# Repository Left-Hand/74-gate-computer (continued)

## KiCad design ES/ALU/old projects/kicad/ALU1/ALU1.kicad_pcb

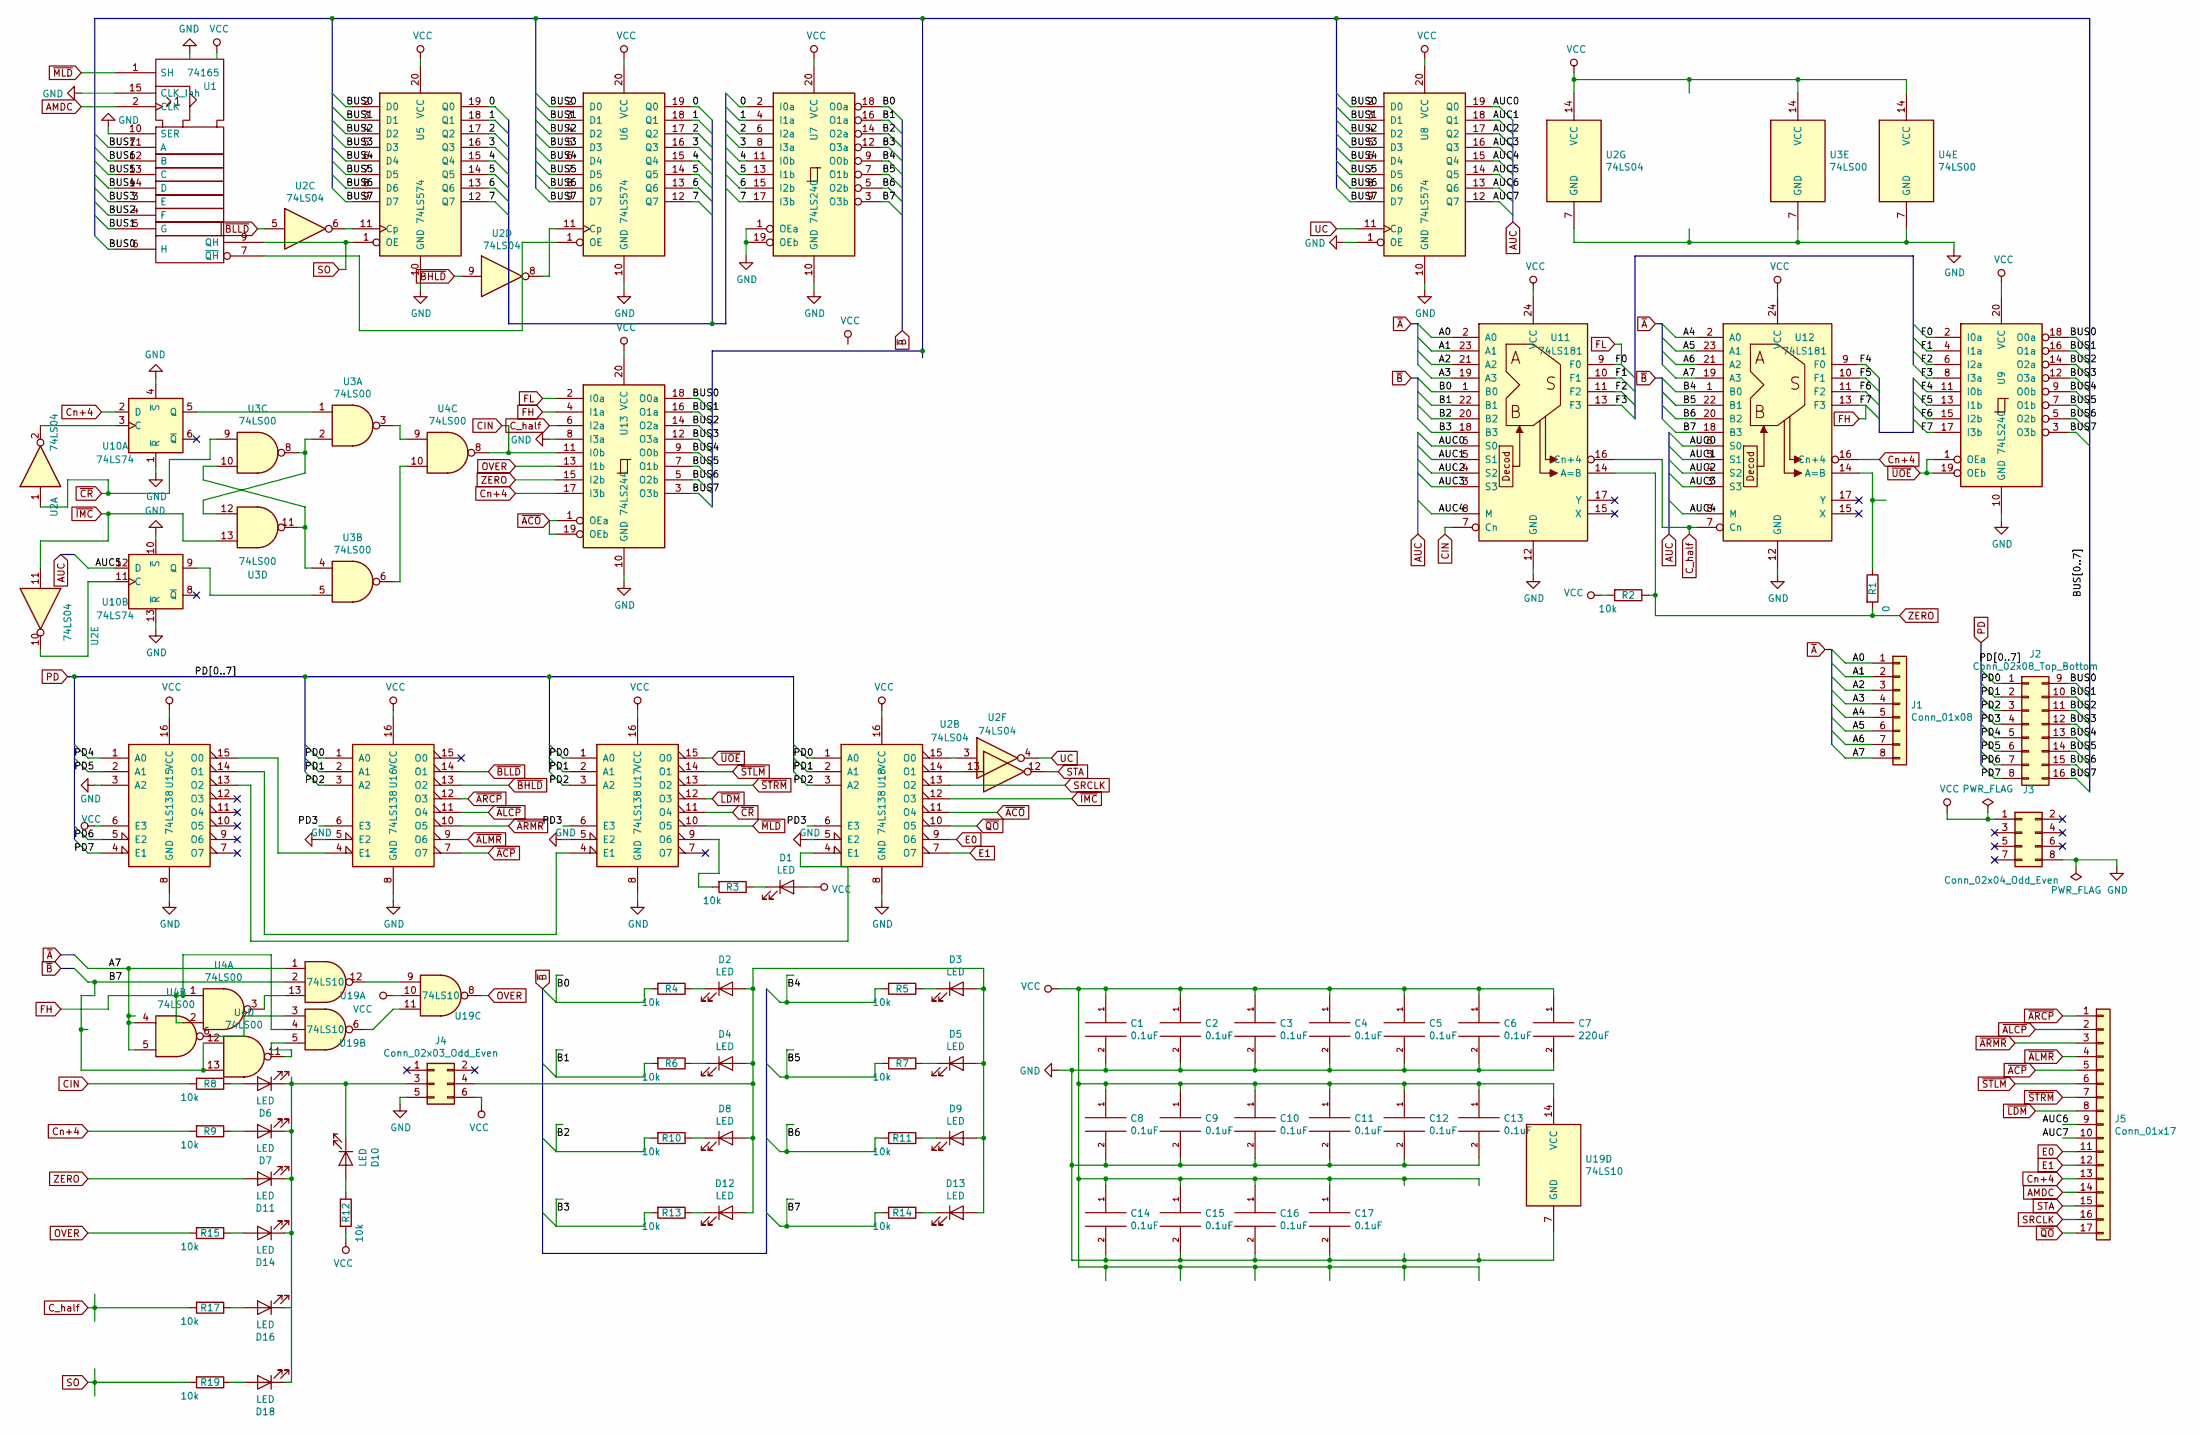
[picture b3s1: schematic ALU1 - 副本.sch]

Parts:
C1, C2, C3, C4, C5, C6, C8, C9, C10, C11, C12, C13, C14, C15, C16, C17: 0.1uF; C_Disc_D5.0mm_W2.5mm_P5.00mm
C7: 220uF; C_Radial_D6.3mm_H7.0mm_P2.50mm
D1, D2, D3, D4, D5, D6, D7, D8, D9, D10, D11, D12, D13, D14, D16, D18: LED; LED_Rectangular_W5.0mm_H2.0mm
J1: Conn_01x08; PinHeader_1x08_P2.54mm_Vertical
J2: Conn_02x08_Top_Bottom; PinHeader_2x08_P2.54mm_Horizontal
J3: Conn_02x04_Odd_Even; PinHeader_2x04_P2.54mm_Horizontal
J4: Conn_02x03_Odd_Even; PinHeader_2x03_P2.54mm_Vertical
J5: Conn_01x17; PinHeader_1x17_P2.54mm_Vertical
R1: 0; R_0805_2012Metric
R2, R3, R4, R5, R6, R7, R8, R9, R10, R11, R12, R13, R14, R15, R17, R19: 10k; R_0805_2012Metric
U1: 74165; DIP-16_W7.62mm
U2: 74LS04; DIP-14_W7.62mm
U3, U4: 74LS00; DIP-14_W7.62mm
U5, U6, U8: 74LS574; DIP-20_W7.62mm
U7, U9: 74LS240; DIP-20_W7.62mm
U10: 74LS74; DIP-14_W7.62mm
U11, U12: 74LS181; DIP-24_W15.24mm
U13: 74LS244; DIP-20_W7.62mm
U15, U16, U17, U18: 74LS138; DIP-16_W7.62mm
U19: 74LS10; DIP-14_W7.62mm

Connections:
/0: U5.19 (Q0), U6.19 (Q0), U7.2 (I0a)
/1: U5.18 (Q1), U6.18 (Q1), U7.4 (I1a)
/2: U5.17 (Q2), U6.17 (Q2), U7.6 (I2a)
/3: U5.16 (Q3), U6.16 (Q3), U7.8 (I3a)
/4: U5.15 (Q4), U6.15 (Q4), U7.11 (I0b)
/5: U5.14 (Q5), U6.14 (Q5), U7.13 (I1b)
/6: U5.13 (Q6), U6.13 (Q6), U7.15 (I2b)
/7: U5.12 (Q7), U6.12 (Q7), U7.17 (I3b)
/A0: J1.1, U11.2 (A0)
/A1: J1.2, U11.23 (A1)
/A2: J1.3, U11.21 (A2)
/A3: J1.4, U11.19 (A3)
/A4: J1.5, U12.2 (A0)
/A5: J1.6, U12.23 (A1)
/A6: J1.7, U12.21 (A2)
/A7: J1.8, U4.4, U4.5, U12.19 (A3), U19.1
/AUC0: U8.19 (Q0), U11.6 (S0), U12.6 (S0)
/AUC1: U8.18 (Q1), U11.5 (S1), U12.5 (S1)
/AUC2: U8.17 (Q2), U11.4 (S2), U12.4 (S2)
/AUC3: U8.16 (Q3), U11.3 (S3), U12.3 (S3)
/AUC4: U8.15 (Q4), U11.8 (M), U12.8 (M)
/AUC5: U8.14 (Q5), U10.12 (D)
/AUC6: J5.9, U8.13 (Q6)
/AUC7: J5.10, U8.12 (Q7)
/B0: R4.2, U7.18 (O0a), U11.1 (B0)
/B1: R6.2, U7.16 (O1a), U11.22 (B1)
/B2: R10.2, U7.14 (O2a), U11.20 (B2)
/B3: R13.2, U7.12 (O3a), U11.18 (B3)
/B4: R5.2, U7.9 (O0b), U12.1 (B0)
/B5: R7.2, U7.7 (O1b), U12.22 (B1)
/B6: R11.2, U7.5 (O2b), U12.20 (B2)
/B7: R14.2, U4.12, U4.13, U7.3 (O3b), U12.18 (B3), U19.2
/BUS0: J2.9, U1.6 (H), U5.2 (D0), U6.2 (D0), U8.2 (D0), U9.18 (O0a), U13.18 (O0a)
/BUS1: J2.10, U1.5 (G), U5.3 (D1), U6.3 (D1), U8.3 (D1), U9.16 (O1a), U13.16 (O1a)
/BUS2: J2.11, U1.4 (F), U5.4 (D2), U6.4 (D2), U8.4 (D2), U9.14 (O2a), U13.14 (O2a)
/BUS3: J2.12, U1.3 (E), U5.5 (D3), U6.5 (D3), U8.5 (D3), U9.12 (O3a), U13.12 (O3a)
/BUS4: J2.13, U1.14 (D), U5.6 (D4), U6.6 (D4), U8.6 (D4), U9.9 (O0b), U13.9 (O0b)
/BUS5: J2.14, U1.13 (C), U5.7 (D5), U6.7 (D5), U8.7 (D5), U9.7 (O1b), U13.7 (O1b)
/BUS6: J2.15, U1.12 (B), U5.8 (D6), U6.8 (D6), U8.8 (D6), U9.5 (O2b), U13.5 (O2b)
/BUS7: J2.16, U1.11 (A), U5.9 (D7), U6.9 (D7), U8.9 (D7), U9.3 (O3b), U13.3 (O3b)
/F1: U9.4 (I1a), U11.10 (F1)
/F2: U9.6 (I2a), U11.11 (F2)
/F3: U9.8 (I3a), U11.13 (F3)
/F4: U9.11 (I0b), U12.9 (F0)
/F5: U9.13 (I1b), U12.10 (F1)
/F6: U9.15 (I2b), U12.11 (F2)
/PD0: J2.1, U16.1 (A0), U17.1 (A0), U18.1 (A0)
/PD1: J2.2, U16.2 (A1), U17.2 (A1), U18.2 (A1)
/PD2: J2.3, U16.3 (A2), U17.3 (A2), U18.3 (A2)
/PD3: J2.4, U16.6 (E3), U17.6 (E3), U18.6 (E3)
/PD4: J2.5, U15.1 (A0)
/PD5: J2.6, U15.2 (A1)
/PD6: J2.7, U15.5 (E2)
/PD7: J2.8, U15.4 (E1)
AMDC: J5.14, U1.2 (CLK)
CIN: R8.2, U4.8, U11.7 (Cn), U13.11 (I0b)
C_half: R17.2, U11.16 (Cn+4), U12.7 (Cn), U13.6 (I2a)
Cn+4: J5.13, R9.2, U10.2 (D), U12.16 (Cn+4), U13.17 (I3b)
E0: J5.11, U18.9 (O6)
E1: J5.12, U18.7 (O7)
FH: U4.1, U4.2, U9.17 (I3b), U12.13 (F3), U13.4 (I1a), U19.4
FL: U9.2 (I0a), U11.9 (F0), U13.2 (I0a)
GND: C1.2, C2.2, C3.2, C4.2, C5.2, C6.2, C7.2, C8.2, C9.2, C10.2, C11.2, C12.2, C13.2, C14.2, C15.2, C16.2, C17.2, J3.8, J4.5, U1.8 (GND), U1.10 (SER), U1.15 (CLK_Inh), U2.7 (GND), U3.7 (GND), U4.7 (GND), U5.10 (GND), U6.10 (GND), U7.1 (OEa), U7.10 (GND), U7.19 (OEb), U8.1 (OE), U8.10 (GND), U9.10 (GND), U10.1 (~R), U10.4 (~S), U10.10 (~S), U10.13 (~R), U11.12 (GND), U12.12 (GND), U13.8 (I3a), U13.10 (GND), U15.3 (A2), U15.8 (GND), U16.5 (E2), U16.8 (GND), U17.5 (E2), U17.8 (GND), U18.5 (E2), U18.8 (GND), U19.7 (GND); also elsewhere on the board
unnamed: D1.1 (K), R3.1
unnamed: D2.1 (K), R4.1
unnamed: D3.1 (K), R5.1
unnamed: D4.1 (K), R6.1
unnamed: D5.1 (K), R7.1
unnamed: D6.2 (A), R8.1
unnamed: D7.2 (A), R9.1
unnamed: D8.1 (K), R10.1
unnamed: D9.1 (K), R11.1
unnamed: D6.1 (K), D7.1 (K), D10.1 (K), D11.1 (K), D14.1 (K), D16.1 (K), D18.1 (K), J4.3
unnamed: D10.2 (A), R12.1
unnamed: D12.1 (K), R13.1
unnamed: D2.2 (A), D3.2 (A), D4.2 (A), D5.2 (A), D8.2 (A), D9.2 (A), D12.2 (A), D13.2 (A), J4.4
unnamed: D13.1 (K), R14.1
unnamed: D14.2 (A), R15.1
unnamed: D16.2 (A), R17.1
unnamed: D18.2 (A), R19.1
unnamed: R1.1, U12.14 (A=B)
unnamed: R3.2, U17.9 (O6)
unnamed: U1.7 (~QH), U6.1 (OE)
unnamed: U2.6, U5.11 (Cp)
unnamed: U2.8, U6.11 (Cp)
unnamed: U3.3, U4.9
unnamed: U3.6, U4.10
unnamed: U3.4, U3.10, U3.11
unnamed: U3.2, U3.8, U3.12
unnamed: U2.2, U10.3 (C)
unnamed: U3.1, U10.5 (Q)
unnamed: U3.5, U10.9 (Q)
unnamed: U2.10, U10.11 (C)
unnamed: U15.13 (O2), U18.4 (E1)
unnamed: U15.14 (O1), U17.4 (E1)
unnamed: U15.15 (O0), U16.4 (E1)
unnamed: U2.13, U18.14 (O1)
unnamed: U2.3, U18.15 (O0)
unnamed: U4.6, U19.3
unnamed: U4.11, U19.5
unnamed: U19.6, U19.11
unnamed: U19.9, U19.12
unnamed: U4.3, U19.13
OVER: R15.2, U13.13 (I1b), U19.8
SO: R19.2, U1.9 (QH), U5.1 (OE)
SRCLK: J5.16, U18.13 (O2)
STA: J5.15, U2.12
UC: U2.4, U8.11 (Cp)
VCC: C1.1, C2.1, C3.1, C4.1, C5.1, C6.1, C7.1, C8.1, C9.1, C10.1, C11.1, C12.1, C13.1, C14.1, C15.1, C16.1, C17.1, D1.2 (A), J3.1, J4.6, R2.2, R12.2, U1.16 (VCC), U2.14 (VCC), U3.14 (VCC), U4.14 (VCC), U5.20 (VCC), U6.20 (VCC), U7.20 (VCC), U8.20 (VCC), U9.20 (VCC), U11.24 (VCC), U12.24 (VCC), U13.20 (VCC), U15.6 (E3), U15.16 (VCC), U16.16 (VCC), U17.16 (VCC), U18.16 (VCC), U19.10, U19.14 (VCC); also elsewhere on the board
ZERO: D11.2 (A), R1.2, R2.1, U11.14 (A=B), U13.15 (I2b)
~ACO: U13.1 (OEa), U13.19 (OEb), U18.11 (O4)
~ACP: J5.5, U16.7 (O7)
~ALCP: J5.2, U16.11 (O4)
~ALMR: J5.4, U16.9 (O6)
~ARCP: J5.1, U16.12 (O3)
~ARMR: J5.3, U16.10 (O5)
~BHLD: U2.9, U16.13 (O2)
~BLLD: U2.5, U16.14 (O1)
~CR: U2.1, U3.9, U17.11 (O4)
~IMC: U2.11, U3.13, U18.12 (O3)
~LDM: J5.8, U17.12 (O3)
~MLD: U1.1 (SH), U17.10 (O5)
~QO: J5.17, U18.10 (O5)
~STLM: J5.6, U17.14 (O1)
~STRM: J5.7, U17.13 (O2)
~UOE: U9.1 (OEa), U9.19 (OEb), U17.15 (O0)

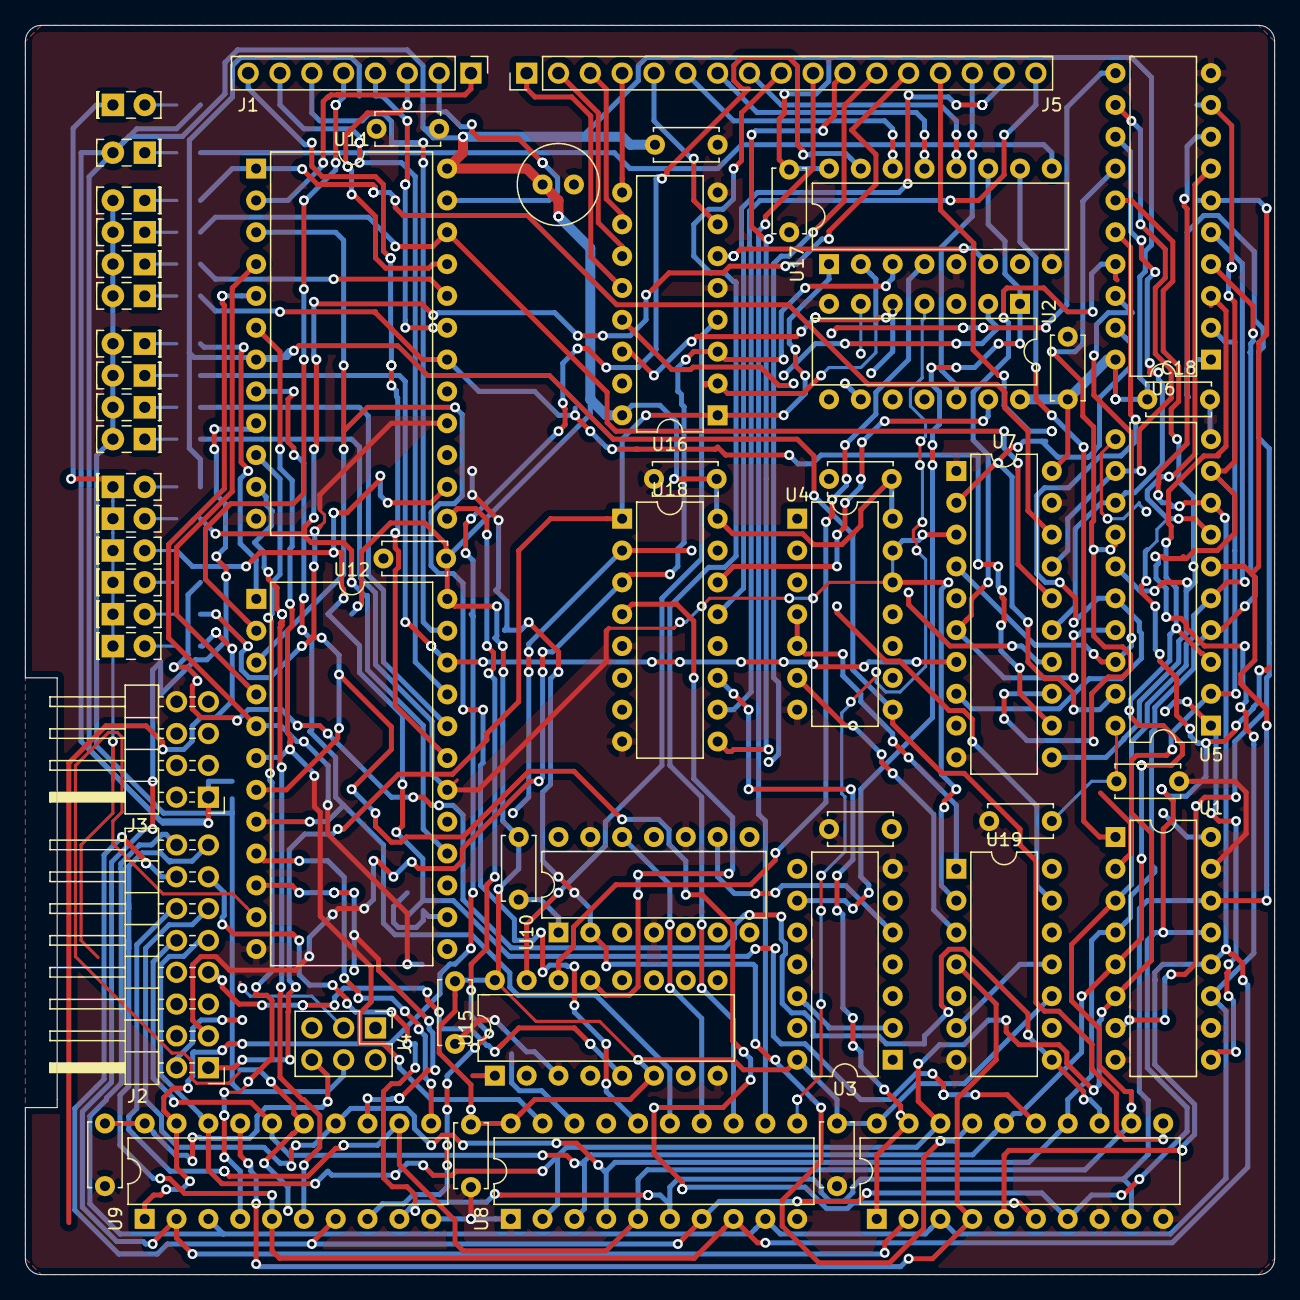
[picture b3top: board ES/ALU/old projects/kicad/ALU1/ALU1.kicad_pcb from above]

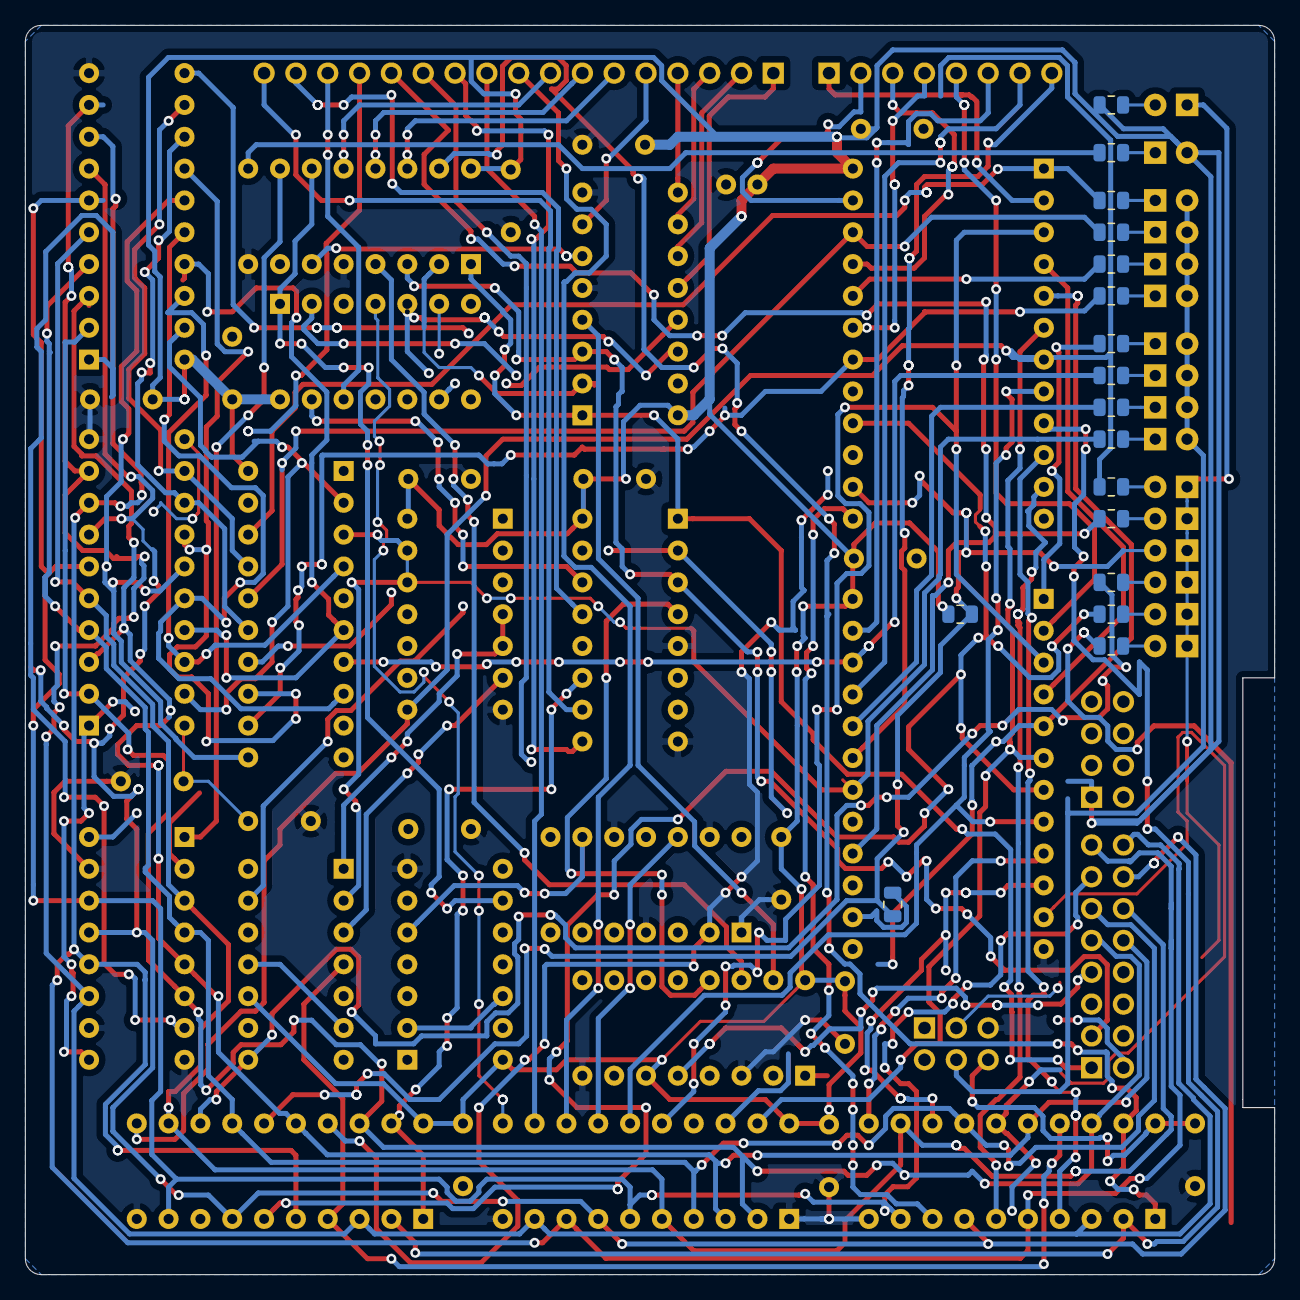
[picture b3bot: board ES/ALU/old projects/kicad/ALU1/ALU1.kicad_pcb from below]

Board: 2 copper layers, 99.7 x 99.7 mm, 73 parts (17 on the bottom side), 126 nets.

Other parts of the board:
C18: 0.1uF; C_Disc_D5.0mm_W2.5mm_P5.00mm

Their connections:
GND: C18.2; also elsewhere on the board
VCC: C18.1; also elsewhere on the board

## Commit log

2020-02-24 Add files via upload
    新增ALU的电路图以及PCB
2020-02-24 Add files via upload
    DIGITAL 文件，用于仿真
2020-03-15 Add files via upload
    vga display card
2020-03-29 Add files via upload
    更新了所有文件
2020-03-29 Create kicad
2020-03-29 Create test
2020-03-29 Update: first working version
